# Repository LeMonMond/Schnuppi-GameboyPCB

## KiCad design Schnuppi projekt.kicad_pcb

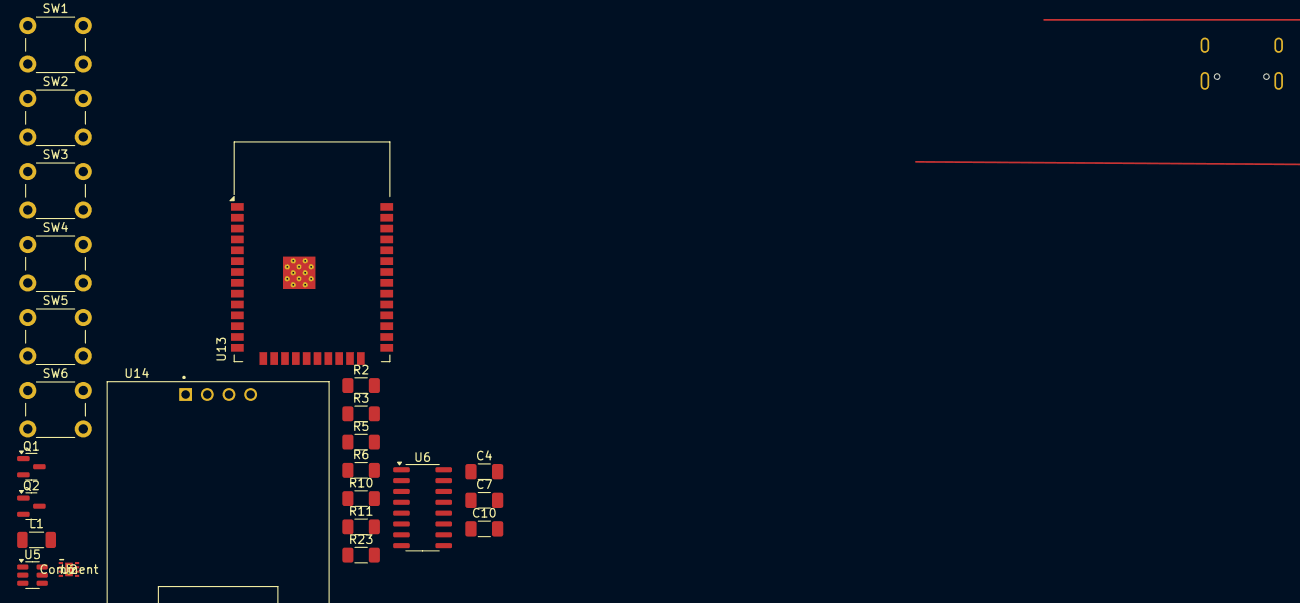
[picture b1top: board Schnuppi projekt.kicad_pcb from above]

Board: 2 copper layers, 25 parts (1 on the bottom side), 26 nets, no tracks yet.

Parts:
C4: 100nF; C_1206_3216Metric_Pad1.33x1.80mm_HandSolder
C7, C10: 10uF; C_1206_3216Metric_Pad1.33x1.80mm_HandSolder
J1: USB4105-GF-A; GCT_USB4105-GF-A
L1: 1uH; L_1206_3216Metric_Pad1.22x1.90mm_HandSolder
Q1, Q2: BC817; SOT-23
R2: 820k; R_1206_3216Metric_Pad1.30x1.75mm_HandSolder
R3: 182k; R_1206_3216Metric_Pad1.30x1.75mm_HandSolder
R5, R6: 5.1k; R_1206_3216Metric_Pad1.30x1.75mm_HandSolder
R10, R11, R23: 10k; R_1206_3216Metric_Pad1.30x1.75mm_HandSolder
SW1, SW2, SW3, SW4, SW5, SW6: SW_Push; SW_PUSH_6mm_H4.3mm
U2: TPS62065DSGR; DSG0008A
U5: WE-TVS-82400102; SOT-23-6
U6: CH340C; SOIC-16_3.9x9.9mm_P1.27mm
U13: ESP32-WROOM-32E; ESP32-WROOM-32D
U14: DM-OLED096-636; MODULE_DM-OLED096-636

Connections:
+3,3V: C10.1, L1.2, R2.1, R23.1, U13.2 (VDD), U14.2 (VCC_IN)
+5V: C7.1, J1.A4_B9 (VBUS), J1.B4_A9 (VBUS), U2.5 (EN), U2.7 (AVIN), U2.8 (PVIN), U5.5, U6.16 (VCC)
Boot/GPIO9: Q2.3 (C), U13.25 (IO0)
CHIP_EN: Q1.3 (C), R23.2, U13.3 (EN)
DTR: Q2.2 (E), R10.1, U6.13 (~DTR)
GND: C4.2, C7.2, C10.2, J1.A1_B12 (GND), J1.B1_A12 (GND), J1.SH1 (SHELL_GND), J1.SH2 (SHELL_GND), J1.SH3 (SHELL_GND), J1.SH4 (SHELL_GND), R3.2, R5.2, R6.2, SW1.2, SW2.2, SW3.2, SW4.2, SW5.2, SW6.2, U2.1 (PGND), U2.3 (AGND), U2.6 (MODE), U2.9 (PAD), U5.2, U6.1 (GND), U13.1 (GND), U13.15 (GND), U13.38 (GND), U13.39 (GND), U14.1 (GND)
Gpio26: SW1.1, U13.11 (IO26)
Gpio27: SW2.1, U13.12 (IO27)
Gpio32: SW3.1, U13.8 (IO32)
Gpio33: SW4.1, U13.9 (IO33)
Gpio34: SW5.1, U13.6 (IO34)
Gpio35: SW6.1, U13.7 (IO35)
unnamed: J1.A5 (CC1), R5.1
unnamed: J1.B5 (CC2), R6.1
unnamed: J1.A7 (DN1), J1.B7 (DN2), U5.1
unnamed: J1.A6 (DP1), J1.B6 (DP2), U5.3
unnamed: Q1.1 (B), R10.2
unnamed: Q2.1 (B), R11.2
unnamed: R2.2, R3.1, U2.4 (FB)
unnamed: L1.1, U2.2 (SW)
unnamed: U5.4, U6.5 (UD+)
unnamed: U5.6, U6.6 (UD-)
unnamed: C4.1, U6.4 (V3)
RTS: Q1.2 (E), R11.1, U6.14 (~RTS)
SCL: U13.36 (IO22), U14.3 (SCL)
SDA: U13.33 (IO21), U14.4 (SDA)

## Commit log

2025-04-07 intial commit
2025-04-07 Button changed
2025-04-07 changed resistors
2025-04-07 added footprints for resistors
2025-04-10 added new footprints
